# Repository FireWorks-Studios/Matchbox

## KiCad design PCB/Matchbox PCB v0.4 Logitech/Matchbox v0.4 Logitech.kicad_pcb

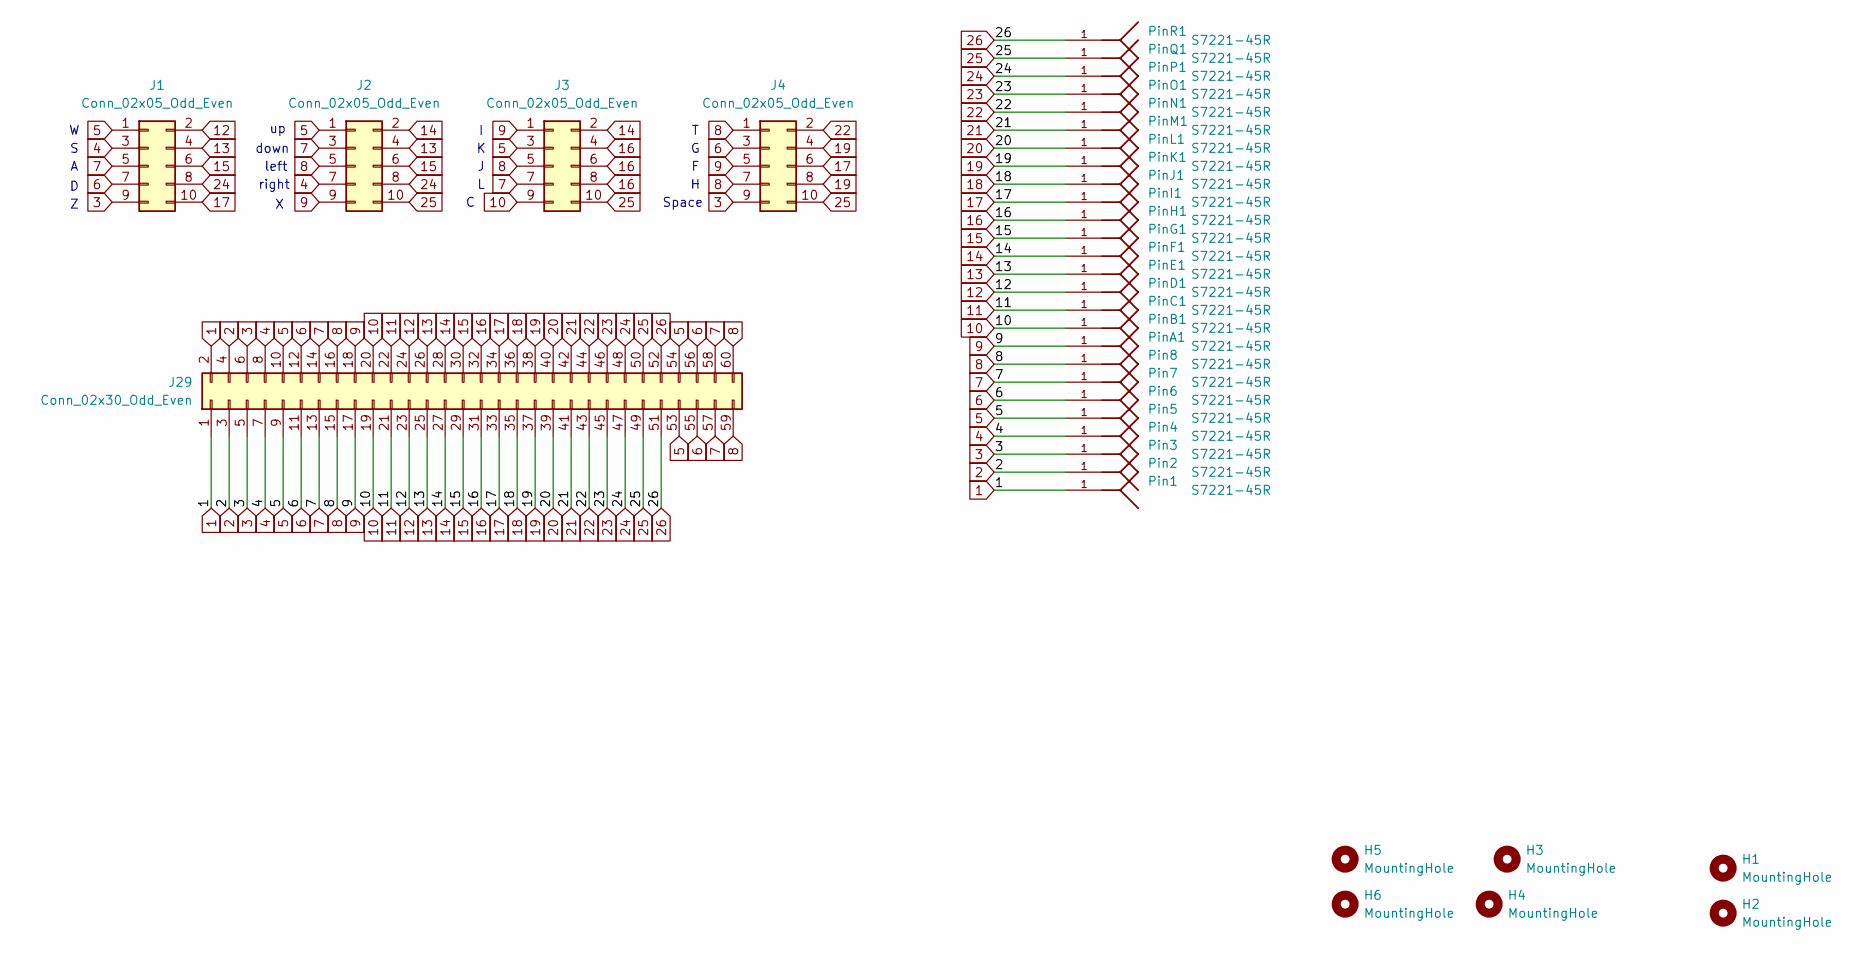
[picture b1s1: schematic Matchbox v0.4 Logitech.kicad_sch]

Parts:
H1, H2: MountingHole; MountingHole_3.7mm
H3, H4, H5, H6: MountingHole; MountingHole_3.2mm_M3
J1, J2, J3, J4: Conn_02x05_Odd_Even; PinHeader_2x05_P2.54mm_Vertical
J29: Conn_02x30_Odd_Even; PinHeader_2x30_P2.54mm_Vertical
Pin1, Pin2, Pin3, Pin4, Pin5, Pin6, Pin7, Pin8: S7221-45R; Ma
PinA1: S7221-45R; Ma
PinB1: S7221-45R; Ma
PinC1: S7221-45R; Ma
PinD1: S7221-45R; Ma
PinE1: S7221-45R; Ma
PinF1: S7221-45R; Ma
PinG1: S7221-45R; Ma
PinH1: S7221-45R; Ma
PinI1: S7221-45R; Ma
PinJ1: S7221-45R; Ma
PinK1: S7221-45R; Ma
PinL1: S7221-45R; Ma
PinM1: S7221-45R; Ma
PinN1: S7221-45R; Ma
PinO1: S7221-45R; Ma
PinP1: S7221-45R; Ma
PinQ1: S7221-45R; Ma
PinR1: S7221-45R; Ma

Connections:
1: J29.1, J29.2, Pin1.1
2: J29.3, J29.4, Pin2.1
3: J1.9, J4.9, J29.5, J29.6, Pin3.1
4: J1.3, J2.7, J29.7, J29.8, Pin4.1
5: J1.1, J2.1, J3.3, J29.9, J29.10, J29.53, J29.54, Pin5.1
6: J1.7, J4.3, J29.11, J29.12, J29.55, J29.56, Pin6.1
7: J1.5, J2.3, J3.7, J29.13, J29.14, J29.57, J29.58, Pin7.1
8: J2.5, J3.5, J4.1, J4.7, J29.15, J29.16, J29.59, J29.60, Pin8.1
9: J2.9, J3.1, J4.5, J29.17, J29.18, PinA1.1
10: J3.9, J29.19, J29.20, PinB1.1
11: J29.21, J29.22, PinC1.1
12: J1.2, J29.23, J29.24, PinD1.1
13: J1.4, J2.4, J29.25, J29.26, PinE1.1
14: J2.2, J3.2, J29.27, J29.28, PinF1.1
15: J1.6, J2.6, J29.29, J29.30, PinG1.1
16: J3.4, J3.6, J3.8, J29.31, J29.32, PinH1.1
17: J1.10, J4.6, J29.33, J29.34, PinI1.1
18: J29.35, J29.36, PinJ1.1
19: J4.4, J4.8, J29.37, J29.38, PinK1.1
20: J29.39, J29.40, PinL1.1
21: J29.41, J29.42, PinM1.1
22: J4.2, J29.43, J29.44, PinN1.1
23: J29.45, J29.46, PinO1.1
24: J1.8, J2.8, J29.47, J29.48, PinP1.1
25: J2.10, J3.10, J4.10, J29.49, J29.50, PinQ1.1
26: J29.51, J29.52, PinR1.1

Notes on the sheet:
right
down
left
Space

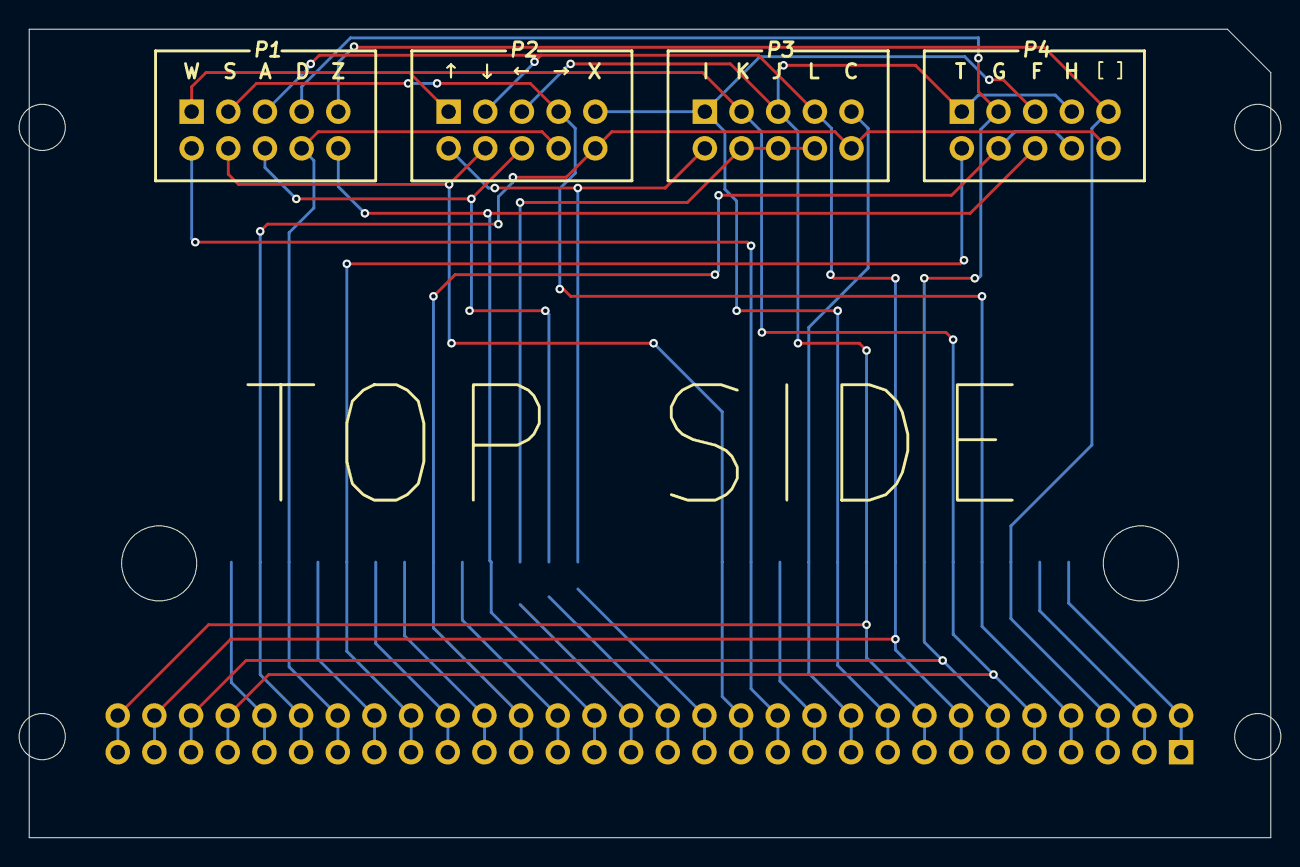
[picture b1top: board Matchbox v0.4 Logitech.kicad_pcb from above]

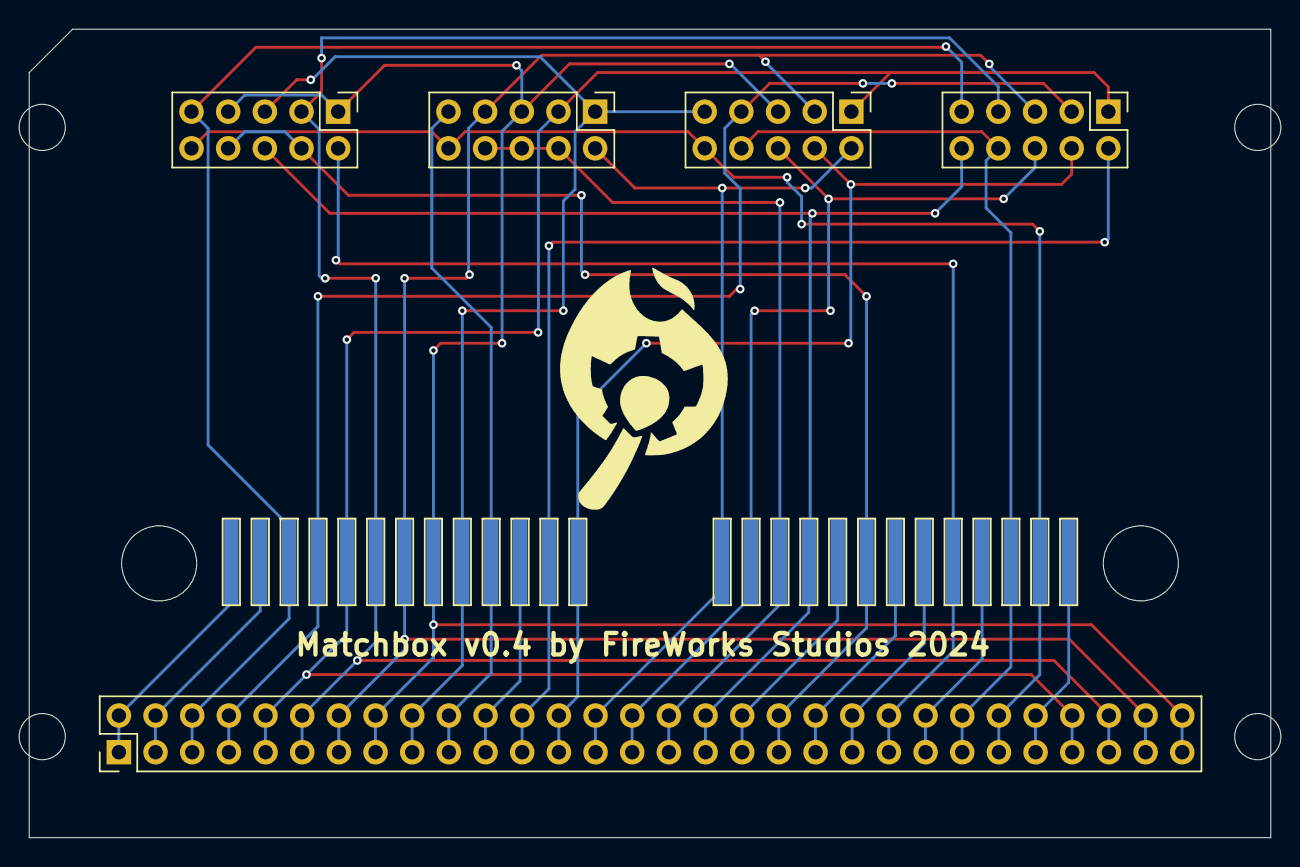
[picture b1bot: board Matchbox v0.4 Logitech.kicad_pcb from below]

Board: 2 copper layers, 86.0 x 56.0 mm, 38 parts (38 on the bottom side), 26 nets.

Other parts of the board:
G1: LOGO; kicad_pic_19mm_19mm

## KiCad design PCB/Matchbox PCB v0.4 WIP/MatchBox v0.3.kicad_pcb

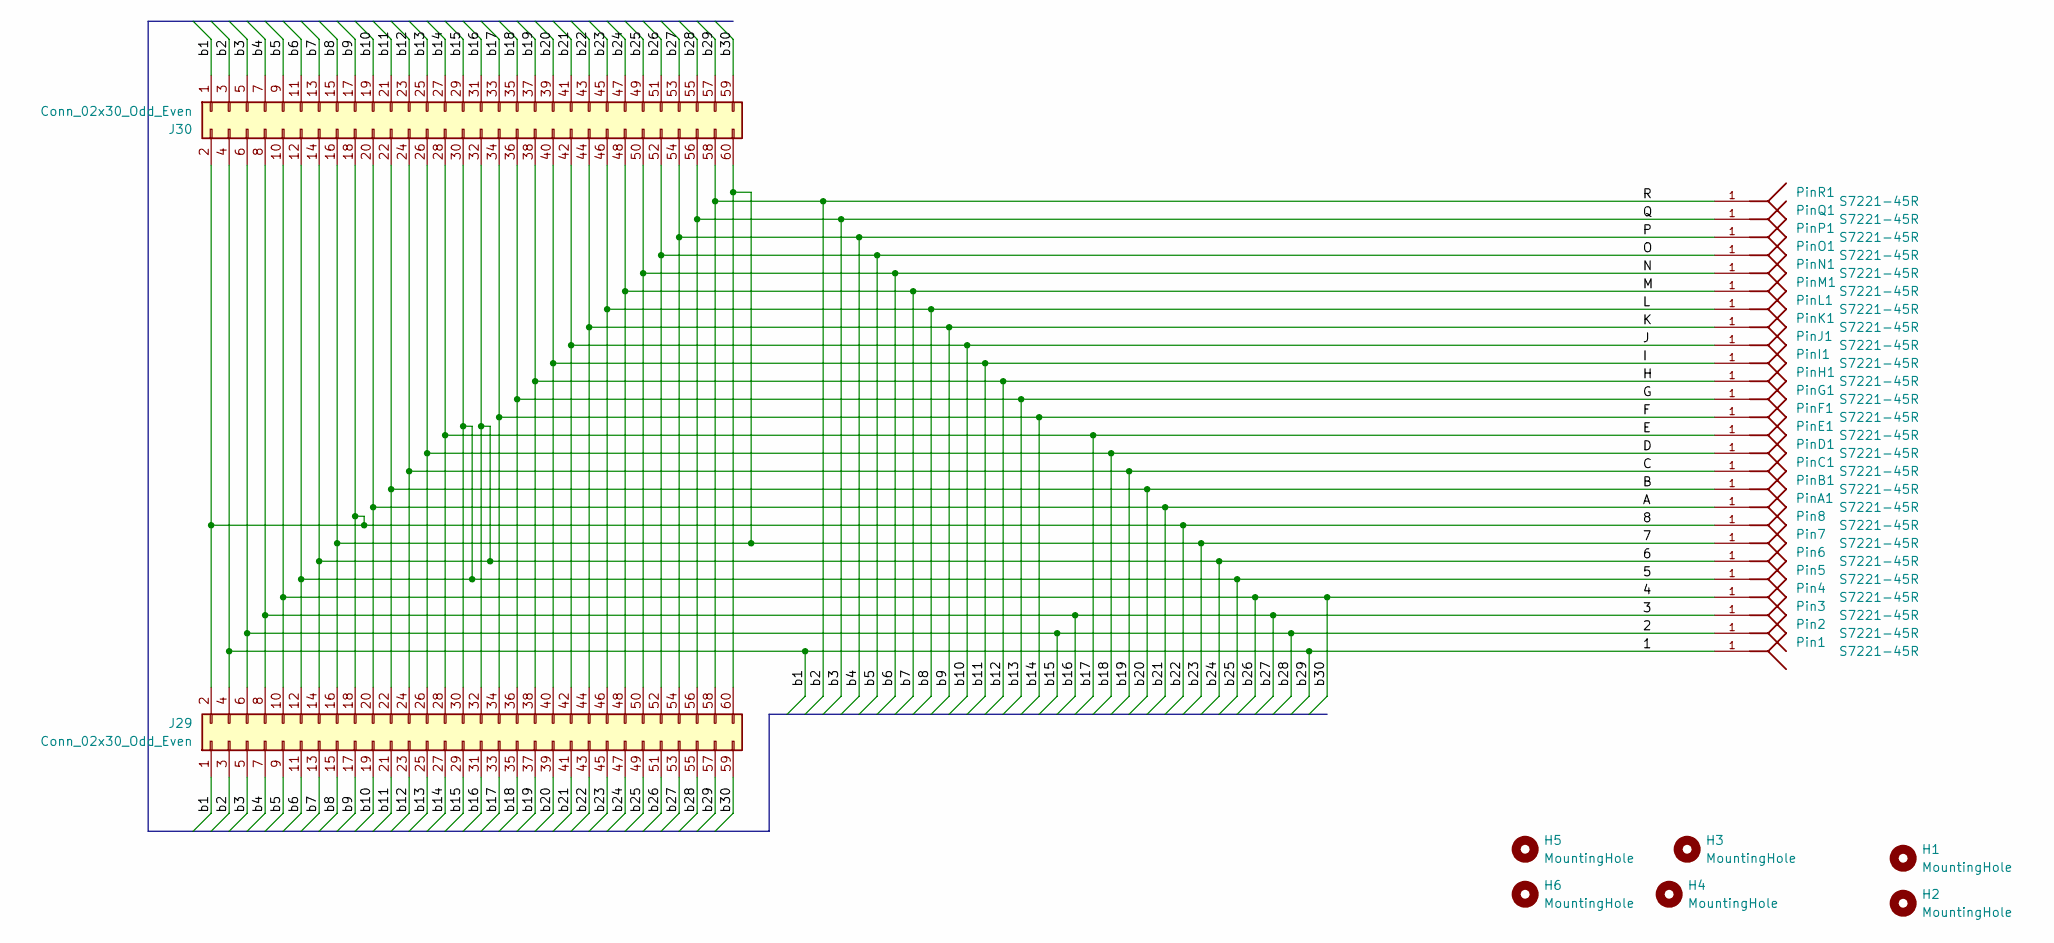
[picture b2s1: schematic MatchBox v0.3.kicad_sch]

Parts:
H1, H2: MountingHole; MountingHole_3.7mm
H3, H4, H5, H6: MountingHole; MountingHole_3.2mm_M3
J29, J30: Conn_02x30_Odd_Even; PinHeader_2x30_P2.54mm_Vertical
Pin1, Pin2, Pin3, Pin4, Pin5, Pin6, Pin7, Pin8: S7221-45R; HARWIN_S7221-45R
PinA1: S7221-45R; HARWIN_S7221-45R
PinB1: S7221-45R; HARWIN_S7221-45R
PinC1: S7221-45R; HARWIN_S7221-45R
PinD1: S7221-45R; HARWIN_S7221-45R
PinE1: S7221-45R; HARWIN_S7221-45R
PinF1: S7221-45R; HARWIN_S7221-45R
PinG1: S7221-45R; HARWIN_S7221-45R
PinH1: S7221-45R; HARWIN_S7221-45R
PinI1: S7221-45R; HARWIN_S7221-45R
PinJ1: S7221-45R; HARWIN_S7221-45R
PinK1: S7221-45R; HARWIN_S7221-45R
PinL1: S7221-45R; HARWIN_S7221-45R
PinM1: S7221-45R; HARWIN_S7221-45R
PinN1: S7221-45R; HARWIN_S7221-45R
PinO1: S7221-45R; HARWIN_S7221-45R
PinP1: S7221-45R; HARWIN_S7221-45R
PinQ1: S7221-45R; HARWIN_S7221-45R
PinR1: S7221-45R; HARWIN_S7221-45R

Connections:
/1: J29.1, J29.4, J29.57, J30.1, J30.4, J30.57, Pin1.1
/2: J29.6, J29.29, J29.55, J30.6, J30.29, J30.55, Pin2.1
/3: J29.8, J29.31, J29.53, J30.8, J30.31, J30.53, Pin3.1
/4: J29.10, J29.51, J29.59, J30.10, J30.51, J30.59, Pin4.1
/5: J29.12, J29.30, J29.49, J30.12, J30.30, J30.49, Pin5.1
/6: J29.14, J29.32, J29.47, J30.14, J30.32, J30.47, Pin6.1
/7: J29.16, J29.45, J29.60, J30.16, J30.45, J30.60, Pin7.1
/8: J29.2, J29.18, J29.43, J30.2, J30.18, J30.43, Pin8.1
/A: J29.20, J29.41, J30.20, J30.41, PinA1.1
/B: J29.22, J29.39, J30.22, J30.39, PinB1.1
/C: J29.24, J29.37, J30.24, J30.37, PinC1.1
/D: J29.26, J29.35, J30.26, J30.35, PinD1.1
/E: J29.28, J29.33, J30.28, J30.33, PinE1.1
/F: J29.27, J29.34, J30.27, J30.34, PinF1.1
/G: J29.25, J29.36, J30.25, J30.36, PinG1.1
/H: J29.23, J29.38, J30.23, J30.38, PinH1.1
/I: J29.21, J29.40, J30.21, J30.40, PinI1.1
/J: J29.19, J29.42, J30.19, J30.42, PinJ1.1
/K: J29.17, J29.44, J30.17, J30.44, PinK1.1
/L: J29.15, J29.46, J30.15, J30.46, PinL1.1
/M: J29.13, J29.48, J30.13, J30.48, PinM1.1
/N: J29.11, J29.50, J30.11, J30.50, PinN1.1
/O: J29.9, J29.52, J30.9, J30.52, PinO1.1
/P: J29.7, J29.54, J30.7, J30.54, PinP1.1
/Q: J29.5, J29.56, J30.5, J30.56, PinQ1.1
/R: J29.3, J29.58, J30.3, J30.58, PinR1.1

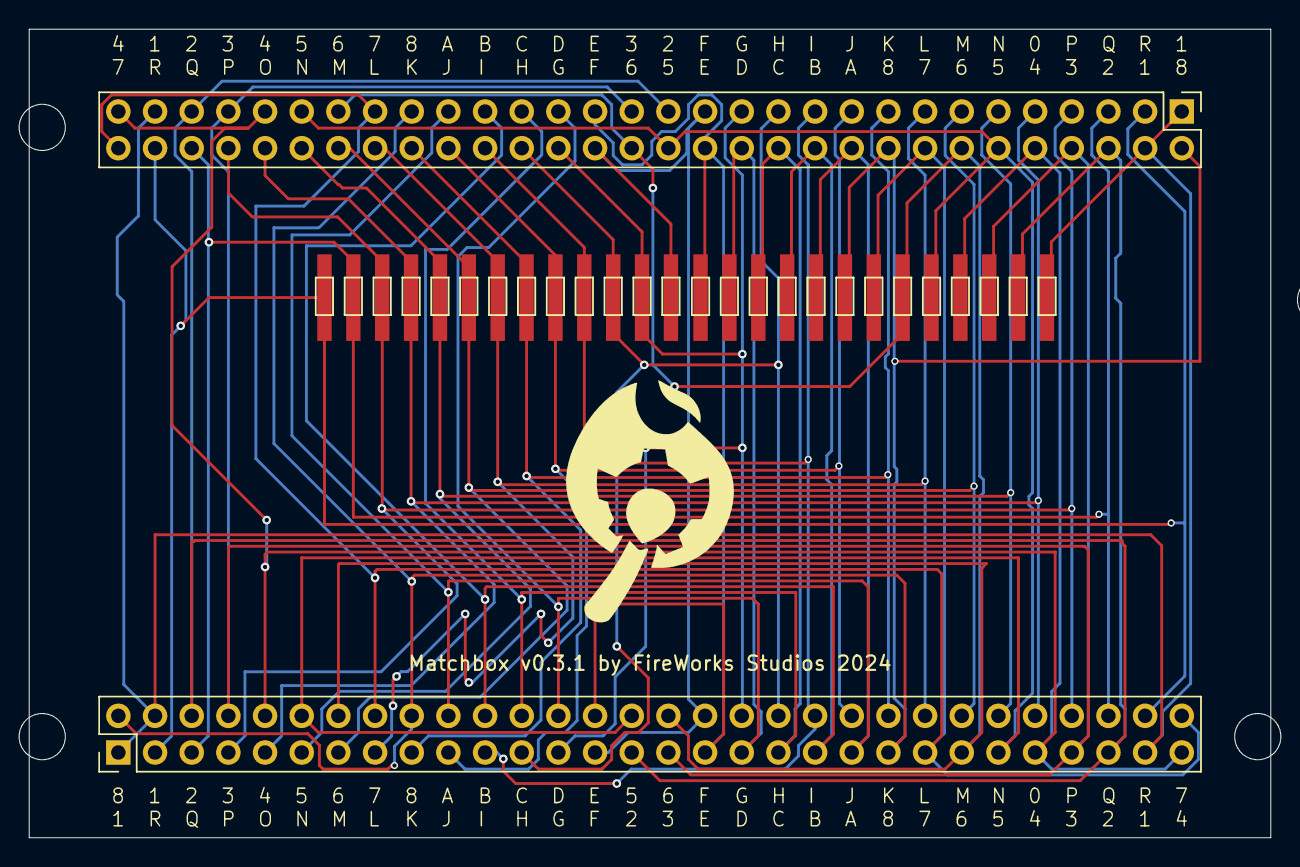
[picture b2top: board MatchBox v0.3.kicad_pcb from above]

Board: 2 copper layers, 86.0 x 56.0 mm, 36 parts (1 on the bottom side), 26 nets.

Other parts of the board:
G1, G1#2: LOGO; kicad_pic_19mm_19mm

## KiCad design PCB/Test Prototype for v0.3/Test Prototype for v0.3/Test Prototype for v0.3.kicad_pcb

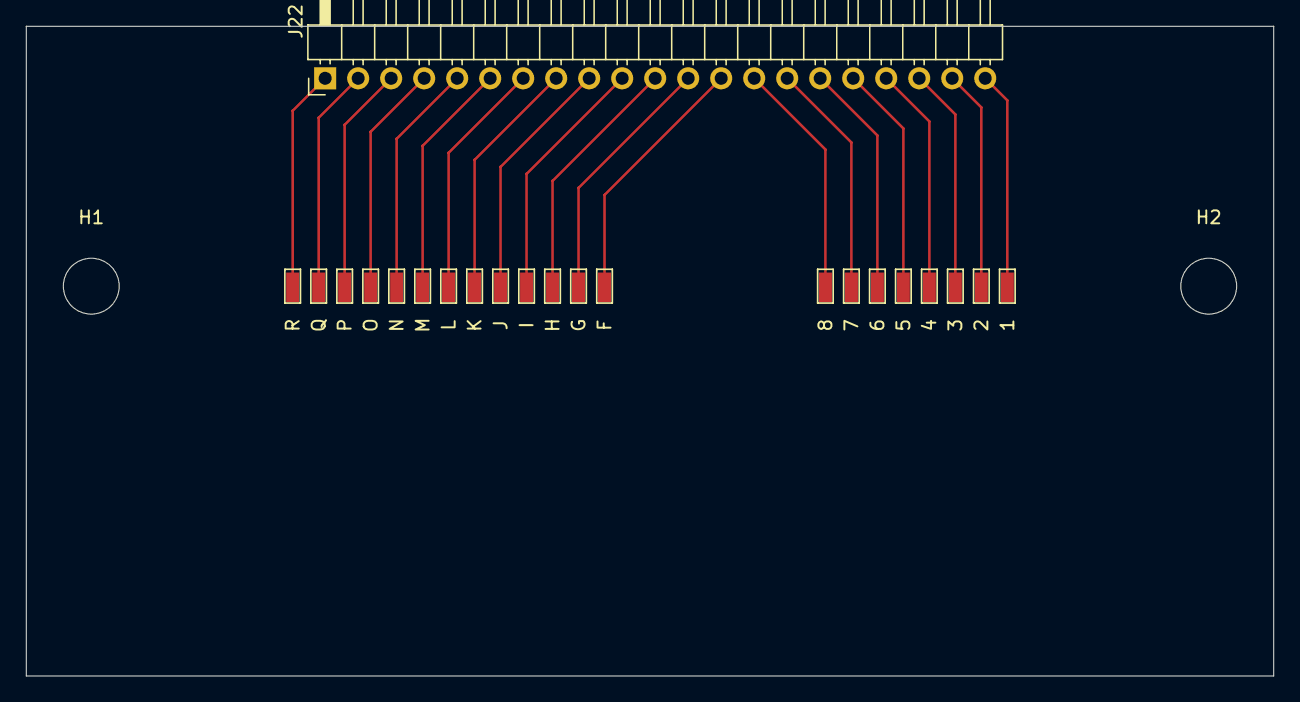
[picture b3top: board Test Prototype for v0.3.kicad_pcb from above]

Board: 2 copper layers, 96.0 x 50.0 mm, 24 parts (0 on the bottom side), 21 nets.

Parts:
1, 2, 3, 4, 5, 6, 7, 8: S7221-45R; HARWIN_S7221-45R
F: S7221-45R; HARWIN_S7221-45R
G: S7221-45R; HARWIN_S7221-45R
H: S7221-45R; HARWIN_S7221-45R
H1, H2: MountingHole; MountingHole_4.3mm_M4
I: S7221-45R; HARWIN_S7221-45R
J: S7221-45R; HARWIN_S7221-45R
J22: Conn_01x21_Socket; PinHeader_1x21_P2.54mm_Horizontal
K: S7221-45R; HARWIN_S7221-45R
L: S7221-45R; HARWIN_S7221-45R
M: S7221-45R; HARWIN_S7221-45R
N: S7221-45R; HARWIN_S7221-45R
O: S7221-45R; HARWIN_S7221-45R
P: S7221-45R; HARWIN_S7221-45R
Q: S7221-45R; HARWIN_S7221-45R
R: S7221-45R; HARWIN_S7221-45R

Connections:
unnamed: J22.1, R.1
unnamed: J22.2, Q.1
unnamed: J22.3, P.1
unnamed: J22.4, O.1
unnamed: J22.5, N.1
unnamed: J22.6, M.1
unnamed: J22.7, L.1
unnamed: J22.8, K.1
unnamed: J.1, J22.9
unnamed: I.1, J22.10
unnamed: H.1, J22.11
unnamed: G.1, J22.12
unnamed: F.1, J22.13
unnamed: 8.1, J22.14
unnamed: 7.1, J22.15
unnamed: 6.1, J22.16
unnamed: 5.1, J22.17
unnamed: 4.1, J22.18
unnamed: 3.1, J22.19
unnamed: 2.1, J22.20
unnamed: 1.1, J22.21

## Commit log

2025-02-10 Matchbox v0.3.1 shell design
2025-02-10 Reorganize folder structure
2025-02-10 PCB archives upload
2025-02-10 Create LICENSE
2025-03-07 Mapping helper webtool v0
2025-03-07 feat: save and load to json
2025-03-07 feat: saves keyboard model info on export
2025-03-12 feat: proper exports and error checking
2025-03-12 restructure software directory
2025-03-12 added some links for documentation site
2025-03-12 updated footer
2025-03-12 exportData has metadata as first obj for better readability
2025-03-12 PCB update: Matchbox v0.4 Logitech PCB
2025-03-12 PCB update : Changing file directory
    moved all gerber folder into a folder call "gerber"
2025-03-12 updated config
2025-03-13 init keyboardmapping with Dell KB 216t
2025-03-13 Software Update: Schematic Helper v0.1 Completed
    Input: Mapping data
    Output: Generated Schematic
2025-03-13 Software Update: Schematic Helper
    output filename changed, pins generate according to metadata in mapping.json
2025-03-13 feat: single entry manual deletion and easier log navigation
2025-04-11 default mapping included
2025-04-16 feat: remapping guide MVP
2025-04-16 test commit
2025-04-16 moved default mapping
2025-04-16 fix: default keyboard mapping path
2025-04-16 test pre-commit command
2025-04-16 testing pre commit
2025-04-16 test pre commit
2025-04-16 testing pre-commit hook
2025-04-16 testing precommit
2025-04-16 testing precommit hook
2025-06-03 Dell KB212-B schematic generated
2025-06-13 feat: instruction site scaffold set up
2025-06-13 add images
2025-06-20 instructions site basic content set up
2025-06-20 feat: keyboard tool ui
2025-06-20 keyboard resizing rule added
2025-06-21 feat: keyboard tool tester functionality
2025-06-21 feat: keyboard tool mapping tooltip
2025-06-22 testing android version
